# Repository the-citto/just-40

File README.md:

# Just 40

A 40% keyboard project, just 40 keys.

Staggered layout

Black unmarked [YMDK ultra slim low profile](https://ymdkey.com/search?q=Ultra-slim+Low+profile) for the control keys

[XVX Skyline R2](https://www.xvxchannel.com/en-gb/collections/low-profile-keycaps/products/xvx-skyline-r2) for alphas (which I like more for feel and sound)

[Waveshare RP2350-Tiny Development Board](https://www.waveshare.com/wiki/RP2350-Tiny)

[NeoPixel Reverse Mount RGB LEDs](https://www.digikey.co.uk/en/products/detail/adafruit-industries-llc/4960/14302512)

[Gateron KS-33 Low Profile 2.0 Banana Switch](https://www.gateron.com/products/gateron-ks-33-low-profile-20-banana-switch?VariantsId=10734)
soldered for plateless mount

PCB developed with KiCAD

Front

Back

#### Alternatives / Inspirations
I've searched for quite some time for 40% offerings, the most interesting to me
 - [Vortex Core Plus](https://vortexgear.store/products/core-plus)
 - [Litl keyboard](https://sthlmkb.com/shop/litl-keyboard-kit/)
 - [Skelett 40](https://novelkeys.com/collections/keyboards/products/skelett-40-keyboard-kit)

## coming soon

Micropython code

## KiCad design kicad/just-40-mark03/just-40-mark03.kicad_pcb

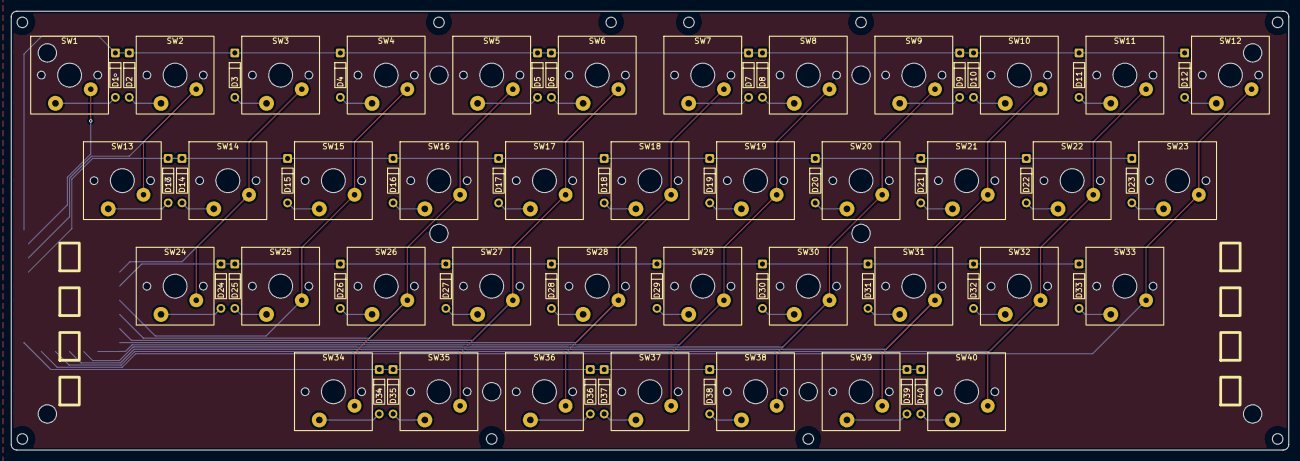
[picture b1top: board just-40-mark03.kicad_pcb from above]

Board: 2 copper layers, 230.0 x 79.0 mm, 100 parts (0 on the bottom side), 56 nets.

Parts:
A1: RP2350-Tiny; RP2350-Tiny-SMD
D1, D2, D3, D4, D5, D6, D7, D8, D9, D10, D11, D12, D13, D14, D15, D16, D17, D18, D19, D20, D21, D22, D23, D24, D25, D26, D27, D28, D29, D30, D31, D32, D33, D34, D35, D36, D37, D38, D39, D40: 1N4148; 1N4148_3
H1, H2, H3, H4, H5, H6, H7, H8: mount-hole; hole-mount
H9: RP2350-Tiny-USB; RP2350-Tiny-USB-3
H10, H11, H12, H13, H14, H15, H16, H17, H18, H19: mount-hole; hole-foot
SW1, SW2, SW3, SW4, SW5, SW6, SW7, SW8, SW9, SW10, SW11, SW12, SW13, SW14, SW15, SW16, SW17, SW18, SW19, SW20, SW21, SW22, SW23, SW24, SW25, SW26, SW27, SW28, SW29, SW30, SW31, SW32, SW33, SW34, SW35, SW36, SW37, SW38, SW39, SW40: KS-33v3-1U_4

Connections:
COL_00_2: A1.1 (GPIO1), SW1.1 (A)
COL_01_2: A1.2 (GPIO2), SW2.1 (A), SW13.1 (A)
COL_02_2: A1.29 (GPIO29_ADC2), SW3.1 (A), SW14.1 (A), SW24.1 (A)
COL_03_2: A1.27 (GPIO27_ADC1), SW4.1 (A), SW15.1 (A), SW25.1 (A)
COL_04_2: A1.26 (GPIO26_ADC0), SW5.1 (A), SW16.1 (A), SW26.1 (A), SW34.1 (A)
COL_05_2: A1.15 (GPIO15), SW6.1 (A), SW17.1 (A), SW27.1 (A), SW35.1 (A)
COL_06_2: A1.14 (GPIO14), SW7.1 (A), SW18.1 (A), SW28.1 (A), SW36.1 (A)
COL_07_2: A1.13 (GPIO13), SW8.1 (A), SW19.1 (A), SW29.1 (A), SW37.1 (A)
COL_08_2: A1.12 (GPIO12), SW9.1 (A), SW20.1 (A), SW30.1 (A), SW38.1 (A)
COL_09_2: A1.11 (GPIO11), SW10.1 (A), SW21.1 (A), SW31.1 (A), SW39.1 (A)
COL_10_2: A1.10 (GPIO10), SW11.1 (A), SW22.1 (A), SW32.1 (A), SW40.1 (A)
COL_11_2: A1.9 (GPIO9), SW12.1 (A), SW23.1 (A), SW33.1 (A)
unnamed: D1.A, SW1.2 (B)
unnamed: D2.A, SW2.2 (B)
unnamed: D3.A, SW3.2 (B)
unnamed: D4.A, SW4.2 (B)
unnamed: D5.A, SW5.2 (B)
unnamed: D6.A, SW6.2 (B)
unnamed: D7.A, SW7.2 (B)
unnamed: D8.A, SW8.2 (B)
unnamed: D9.A, SW9.2 (B)
unnamed: D10.A, SW10.2 (B)
unnamed: D11.A, SW11.2 (B)
unnamed: D12.A, SW12.2 (B)
unnamed: D13.A, SW13.2 (B)
unnamed: D14.A, SW14.2 (B)
unnamed: D15.A, SW15.2 (B)
unnamed: D16.A, SW16.2 (B)
unnamed: D17.A, SW17.2 (B)
unnamed: D18.A, SW18.2 (B)
unnamed: D19.A, SW19.2 (B)
unnamed: D20.A, SW20.2 (B)
unnamed: D21.A, SW21.2 (B)
unnamed: D22.A, SW22.2 (B)
unnamed: D23.A, SW23.2 (B)
unnamed: D24.A, SW24.2 (B)
unnamed: D25.A, SW25.2 (B)
unnamed: D26.A, SW26.2 (B)
unnamed: D27.A, SW27.2 (B)
unnamed: D28.A, SW28.2 (B)
unnamed: D29.A, SW29.2 (B)
unnamed: D30.A, SW30.2 (B)
unnamed: D31.A, SW31.2 (B)
unnamed: D32.A, SW32.2 (B)
unnamed: D33.A, SW33.2 (B)
unnamed: D34.A, SW34.2 (B)
unnamed: D35.A, SW35.2 (B)
unnamed: D36.A, SW36.2 (B)
unnamed: D37.A, SW37.2 (B)
unnamed: D38.A, SW38.2 (B)
unnamed: D39.A, SW39.2 (B)
unnamed: D40.A, SW40.2 (B)
ROW_0_2: A1.0 (GPIO0), D1.K, D2.K, D3.K, D4.K, D5.K, D6.K, D7.K, D8.K, D9.K, D10.K, D11.K, D12.K
ROW_1_2: A1.3 (GPIO3), D13.K, D14.K, D15.K, D16.K, D17.K, D18.K, D19.K, D20.K, D21.K, D22.K, D23.K
ROW_2_2: A1.28 (GPIO28_ADC2), D24.K, D25.K, D26.K, D27.K, D28.K, D29.K, D30.K, D31.K, D32.K, D33.K
ROW_3_2: A1.8 (GPIO8), D34.K, D35.K, D36.K, D37.K, D38.K, D39.K, D40.K

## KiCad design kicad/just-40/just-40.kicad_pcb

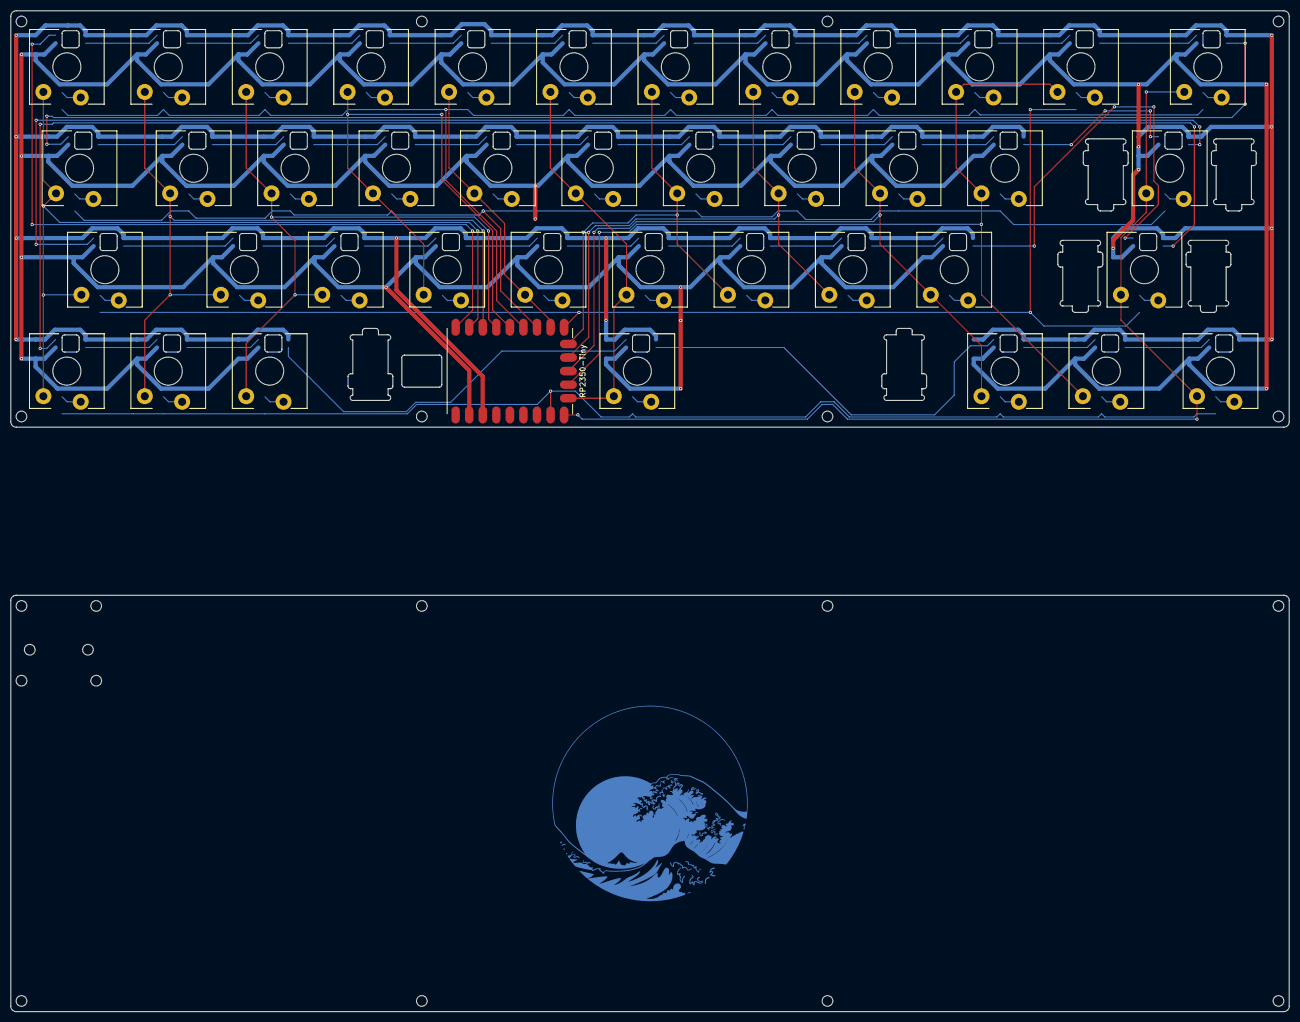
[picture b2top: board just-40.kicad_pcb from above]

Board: 2 copper layers, 239.5 x 78.0 mm, 57 parts (0 on the bottom side), 97 nets.

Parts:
A1, A2, A3, A4, A5, A6, A7, A8, A9, A10, A11, A14, A15, A16, A17, A18, A19, A20, A21, A22, A25, A26, A27, A28, A29, A30, A31, A32, A34, A35, A36, A38, A39: KEY-PARTS-HS; SW-LED-D-center-1U
A12: KEY-PARTS-HS; SW-LED-D-center-1.5U
A13, A40: KEY-PARTS-HS; SW-LED-D-center-1.25U
A23: KEY-PARTS-HS; SW-LED-D-center-2.25U
A24: KEY-PARTS-HS; SW-LED-D-center-1.75U
A33: KEY-PARTS-HS; SW-LED-D-center-2.75U
A37: KEY-PARTS-HS; SW-LED-D-center-6.25U
A41: RP2350-Tiny
H1, H2, H3, H4, H5, H6, H7, H8, H10, H11, H12, H13, H14, H15, H16: mount-hole; Mount-Hole
H9: RP2350-Tiny-USB

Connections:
COL_00: A1.A, A13.A, A24.A, A34.A, A41.1 (GPIO1)
COL_01: A2.A, A14.A, A25.A, A35.A, A41.2 (GPIO2)
COL_02: A3.A, A15.A, A26.A, A36.A, A41.3 (GPIO3)
COL_03: A4.A, A16.A, A27.A, A41.4 (GPIO4)
COL_04: A5.A, A17.A, A28.A, A41.7 (GPIO7)
COL_05: A6.A, A18.A, A29.A, A37.A, A41.13 (GPIO13)
COL_06: A7.A, A19.A, A30.A, A41.9 (GPIO9)
COL_07: A8.A, A20.A, A31.A, A41.10 (GPIO10)
COL_08: A9.A, A21.A, A32.A, A38.A, A41.11 (GPIO11)
COL_09: A10.A, A11.A, A22.A, A39.A, A41.12 (GPIO12)
COL_10: A12.A, A23.A, A33.A, A40.A, A41.14 (GPIO14)
DIN: A1.4 (DIN), A41.0 (GPIO0)
GND: A1.3 (GND), A1.C_1, A2.3 (GND), A2.C_1, A3.3 (GND), A3.C_1, A4.3 (GND), A4.C_1, A5.3 (GND), A5.C_1, A6.3 (GND), A6.C_1, A7.3 (GND), A7.C_1, A8.3 (GND), A8.C_1, A9.3 (GND), A9.C_1, A10.3 (GND), A10.C_1, A11.3 (GND), A11.C_1, A12.3 (GND), A12.C_1, A13.3 (GND), A13.C_1, A14.3 (GND), A14.C_1, A15.3 (GND), A15.C_1, A16.3 (GND), A16.C_1, A17.3 (GND), A17.C_1, A18.3 (GND), A18.C_1, A19.3 (GND), A19.C_1, A20.3 (GND), A20.C_1, A21.3 (GND), A21.C_1, A22.3 (GND), A22.C_1, A23.3 (GND), A23.C_1, A24.3 (GND), A24.C_1, A25.3 (GND), A25.C_1, A26.3 (GND), A26.C_1, A27.3 (GND), A27.C_1, A28.3 (GND), A28.C_1, A29.3 (GND), A29.C_1, A30.3 (GND), A30.C_1, A31.3 (GND), A31.C_1, A32.3 (GND), A32.C_1, A33.3 (GND), A33.C_1, A34.3 (GND), A34.C_1, A35.3 (GND), A35.C_1, A36.3 (GND), A36.C_1, A37.3 (GND), A37.C_1, A38.3 (GND), A38.C_1, A39.3 (GND), A39.C_1, A40.3 (GND), A40.C_1, A41.GND
unnamed: A1.2 (DOUT), A2.4 (DIN)
unnamed: A1.B, A1.D_1
unnamed: A2.2 (DOUT), A3.4 (DIN)
unnamed: A2.B, A2.D_1
unnamed: A3.2 (DOUT), A4.4 (DIN)
unnamed: A3.B, A3.D_1
unnamed: A4.2 (DOUT), A5.4 (DIN)
unnamed: A4.B, A4.D_1
unnamed: A5.2 (DOUT), A6.4 (DIN)
unnamed: A5.B, A5.D_1
unnamed: A6.2 (DOUT), A7.4 (DIN)
unnamed: A6.B, A6.D_1
unnamed: A7.2 (DOUT), A8.4 (DIN)
unnamed: A7.B, A7.D_1
unnamed: A8.2 (DOUT), A9.4 (DIN)
unnamed: A8.B, A8.D_1
unnamed: A9.B, A9.D_1
unnamed: A9.2 (DOUT), A10.4 (DIN)
unnamed: A10.2 (DOUT), A11.4 (DIN)
unnamed: A10.B, A10.D_1
unnamed: A11.2 (DOUT), A12.4 (DIN)
unnamed: A11.B, A11.D_1
unnamed: A12.2 (DOUT), A13.4 (DIN)
unnamed: A12.B, A12.D_1
unnamed: A13.2 (DOUT), A14.4 (DIN)
unnamed: A13.B, A13.D_1
unnamed: A14.2 (DOUT), A15.4 (DIN)
unnamed: A14.B, A14.D_1
unnamed: A15.2 (DOUT), A16.4 (DIN)
unnamed: A15.B, A15.D_1
unnamed: A16.2 (DOUT), A17.4 (DIN)
unnamed: A16.B, A16.D_1
unnamed: A17.2 (DOUT), A18.4 (DIN)
unnamed: A17.B, A17.D_1
unnamed: A18.2 (DOUT), A19.4 (DIN)
unnamed: A18.B, A18.D_1
unnamed: A19.2 (DOUT), A20.4 (DIN)
unnamed: A19.B, A19.D_1
unnamed: A20.2 (DOUT), A21.4 (DIN)
unnamed: A20.B, A20.D_1
unnamed: A21.2 (DOUT), A22.4 (DIN)
unnamed: A21.B, A21.D_1
unnamed: A22.2 (DOUT), A23.4 (DIN)
unnamed: A22.B, A22.D_1
unnamed: A23.2 (DOUT), A24.4 (DIN)
unnamed: A23.B, A23.D_1
unnamed: A24.2 (DOUT), A25.4 (DIN)
unnamed: A24.B, A24.D_1
unnamed: A25.2 (DOUT), A26.4 (DIN)
unnamed: A25.B, A25.D_1
unnamed: A26.2 (DOUT), A27.4 (DIN)
unnamed: A26.B, A26.D_1
unnamed: A27.2 (DOUT), A28.4 (DIN)
unnamed: A27.B, A27.D_1
unnamed: A28.2 (DOUT), A29.4 (DIN)
unnamed: A28.B, A28.D_1
unnamed: A29.2 (DOUT), A30.4 (DIN)
unnamed: A29.B, A29.D_1
unnamed: A30.2 (DOUT), A31.4 (DIN)
unnamed: A30.B, A30.D_1
unnamed: A31.2 (DOUT), A32.4 (DIN)
unnamed: A31.B, A31.D_1
unnamed: A32.2 (DOUT), A33.4 (DIN)
unnamed: A32.B, A32.D_1
unnamed: A33.2 (DOUT), A34.4 (DIN)
unnamed: A33.B, A33.D_1
unnamed: A34.2 (DOUT), A35.4 (DIN)
unnamed: A34.B, A34.D_1
unnamed: A35.2 (DOUT), A36.4 (DIN)
unnamed: A35.B, A35.D_1
unnamed: A36.2 (DOUT), A37.4 (DIN)
unnamed: A36.B, A36.D_1
unnamed: A37.2 (DOUT), A38.4 (DIN)
unnamed: A37.B, A37.D_1
unnamed: A38.2 (DOUT), A39.4 (DIN)
unnamed: A38.B, A38.D_1
unnamed: A39.2 (DOUT), A40.4 (DIN)
unnamed: A39.B, A39.D_1
unnamed: A40.B, A40.D_1
ROW_0: A1.D_2, A2.D_2, A3.D_2, A4.D_2, A5.D_2, A6.D_2, A7.D_2, A8.D_2, A9.D_2, A10.D_2, A12.D_2, A41.5 (GPIO5)
ROW_1: A13.D_2, A14.D_2, A15.D_2, A16.D_2, A17.D_2, A18.D_2, A19.D_2, A20.D_2, A21.D_2, A22.D_2, A23.D_2, A41.6 (GPIO6)
ROW_2: A11.D_2, A24.D_2, A25.D_2, A26.D_2, A27.D_2, A28.D_2, A29.D_2, A30.D_2, A31.D_2, A32.D_2, A33.D_2, A41.8 (GPIO8)
ROW_3: A34.D_2, A35.D_2, A36.D_2, A37.D_2, A38.D_2, A39.D_2, A40.D_2, A41.15 (GPIO15)
V_LED: A1.1 (VDD), A1.C_2, A2.1 (VDD), A2.C_2, A3.1 (VDD), A3.C_2, A4.1 (VDD), A4.C_2, A5.1 (VDD), A5.C_2, A6.1 (VDD), A6.C_2, A7.1 (VDD), A7.C_2, A8.1 (VDD), A8.C_2, A9.1 (VDD), A9.C_2, A10.1 (VDD), A10.C_2, A11.1 (VDD), A11.C_2, A12.1 (VDD), A12.C_2, A13.1 (VDD), A13.C_2, A14.1 (VDD), A14.C_2, A15.1 (VDD), A15.C_2, A16.1 (VDD), A16.C_2, A17.1 (VDD), A17.C_2, A18.1 (VDD), A18.C_2, A19.1 (VDD), A19.C_2, A20.1 (VDD), A20.C_2, A21.1 (VDD), A21.C_2, A22.1 (VDD), A22.C_2, A23.1 (VDD), A23.C_2, A24.1 (VDD), A24.C_2, A25.1 (VDD), A25.C_2, A26.1 (VDD), A26.C_2, A27.1 (VDD), A27.C_2, A28.1 (VDD), A28.C_2, A29.1 (VDD), A29.C_2, A30.1 (VDD), A30.C_2, A31.1 (VDD), A31.C_2, A32.1 (VDD), A32.C_2, A33.1 (VDD), A33.C_2, A34.1 (VDD), A34.C_2, A35.1 (VDD), A35.C_2, A36.1 (VDD), A36.C_2, A37.1 (VDD), A37.C_2, A38.1 (VDD), A38.C_2, A39.1 (VDD), A39.C_2, A40.1 (VDD), A40.C_2, A41.3V3

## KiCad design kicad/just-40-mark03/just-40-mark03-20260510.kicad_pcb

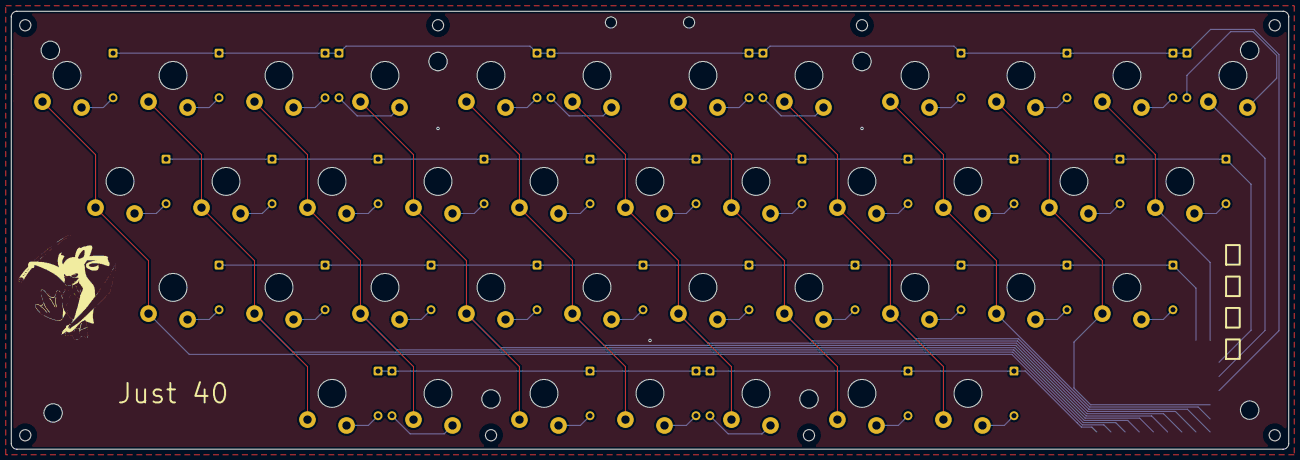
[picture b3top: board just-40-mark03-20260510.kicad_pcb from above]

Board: 2 copper layers, 229.0 x 78.5 mm, 98 parts (0 on the bottom side), 56 nets.

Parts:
A2: RP2350-Zero; RP2350-Tiny-SMD_1
D41, D42, D43, D44, D45, D46, D47, D48, D49, D50, D51, D52, D53, D54, D55, D56, D57, D58, D59, D60, D61, D62, D63, D64, D65, D66, D67, D68, D69, D70, D71, D72, D73, D74, D75, D76, D77, D78, D79, D80: 1N4148
H17, H18, H19, H20, H21, H22, H23, H24: mount-hole; hole-mount
H25, H26, H27, H28, H29, H30, H31, H32: mount-hole; hole-foot
H33: RP2350-Tiny-USB; RP2350-Tiny-USB-3
SW41, SW42, SW43, SW44, SW45, SW46, SW47, SW48, SW49, SW50, SW51, SW52, SW53, SW54, SW55, SW56, SW57, SW58, SW59, SW60, SW61, SW62, SW63, SW64, SW65, SW66, SW67, SW68, SW69, SW70, SW71, SW72, SW73, SW74, SW75, SW76, SW77, SW78, SW79, SW80: KS-33-1U_1

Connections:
COL_800_2: A2.1 (GPIO1), SW41.1 (A), SW53.1 (A), SW64.1 (A)
COL_801_2: A2.2 (GPIO2), SW42.1 (A), SW54.1 (A), SW65.1 (A), SW74.1 (A)
COL_802_2: A2.3 (GPIO3), SW43.1 (A), SW55.1 (A), SW66.1 (A), SW75.1 (A)
COL_803_2: A2.4 (GPIO4), SW44.1 (A), SW56.1 (A), SW67.1 (A), SW76.1 (A)
COL_804_2: A2.5 (GPIO5), SW45.1 (A), SW57.1 (A), SW68.1 (A), SW77.1 (A)
COL_805_2: A2.6 (GPIO6), SW46.1 (A), SW58.1 (A), SW69.1 (A), SW78.1 (A)
COL_806_2: A2.7 (GPIO7), SW47.1 (A), SW59.1 (A), SW70.1 (A), SW79.1 (A)
COL_807_2: A2.8 (GPIO8), SW48.1 (A), SW60.1 (A), SW71.1 (A), SW80.1 (A)
COL_808_2: A2.9 (GPIO9), SW49.1 (A), SW61.1 (A), SW72.1 (A)
COL_809_2: A2.10 (GPIO10), SW50.1 (A), SW62.1 (A), SW73.1 (A)
COL_810_2: A2.14 (GPIO14), SW51.1 (A), SW63.1 (A)
COL_811_2: A2.12 (GPIO12), SW52.1 (A)
unnamed: D41.A, SW41.2 (B)
unnamed: D42.A, SW42.2 (B)
unnamed: D43.A, SW43.2 (B)
unnamed: D44.A, SW44.2 (B)
unnamed: D45.A, SW45.2 (B)
unnamed: D46.A, SW46.2 (B)
unnamed: D47.A, SW47.2 (B)
unnamed: D48.A, SW48.2 (B)
unnamed: D49.A, SW49.2 (B)
unnamed: D50.A, SW50.2 (B)
unnamed: D51.A, SW51.2 (B)
unnamed: D52.A, SW52.2 (B)
unnamed: D53.A, SW53.2 (B)
unnamed: D54.A, SW54.2 (B)
unnamed: D55.A, SW55.2 (B)
unnamed: D56.A, SW56.2 (B)
unnamed: D57.A, SW57.2 (B)
unnamed: D58.A, SW58.2 (B)
unnamed: D59.A, SW59.2 (B)
unnamed: D60.A, SW60.2 (B)
unnamed: D61.A, SW61.2 (B)
unnamed: D62.A, SW62.2 (B)
unnamed: D63.A, SW63.2 (B)
unnamed: D64.A, SW64.2 (B)
unnamed: D65.A, SW65.2 (B)
unnamed: D66.A, SW66.2 (B)
unnamed: D67.A, SW67.2 (B)
unnamed: D68.A, SW68.2 (B)
unnamed: D69.A, SW69.2 (B)
unnamed: D70.A, SW70.2 (B)
unnamed: D71.A, SW71.2 (B)
unnamed: D72.A, SW72.2 (B)
unnamed: D73.A, SW73.2 (B)
unnamed: D74.A, SW74.2 (B)
unnamed: D75.A, SW75.2 (B)
unnamed: D76.A, SW76.2 (B)
unnamed: D77.A, SW77.2 (B)
unnamed: D78.A, SW78.2 (B)
unnamed: D79.A, SW79.2 (B)
unnamed: D80.A, SW80.2 (B)
ROW_80_2: A2.11 (GPIO11), D41.K, D42.K, D43.K, D44.K, D45.K, D46.K, D47.K, D48.K, D49.K, D50.K, D51.K, D52.K
ROW_81_2: A2.13 (GPIO13), D53.K, D54.K, D55.K, D56.K, D57.K, D58.K, D59.K, D60.K, D61.K, D62.K, D63.K
ROW_82_2: A2.15 (GPIO15), D64.K, D65.K, D66.K, D67.K, D68.K, D69.K, D70.K, D71.K, D72.K, D73.K
ROW_83_2: A2.0 (GPIO0), D74.K, D75.K, D76.K, D77.K, D78.K, D79.K, D80.K

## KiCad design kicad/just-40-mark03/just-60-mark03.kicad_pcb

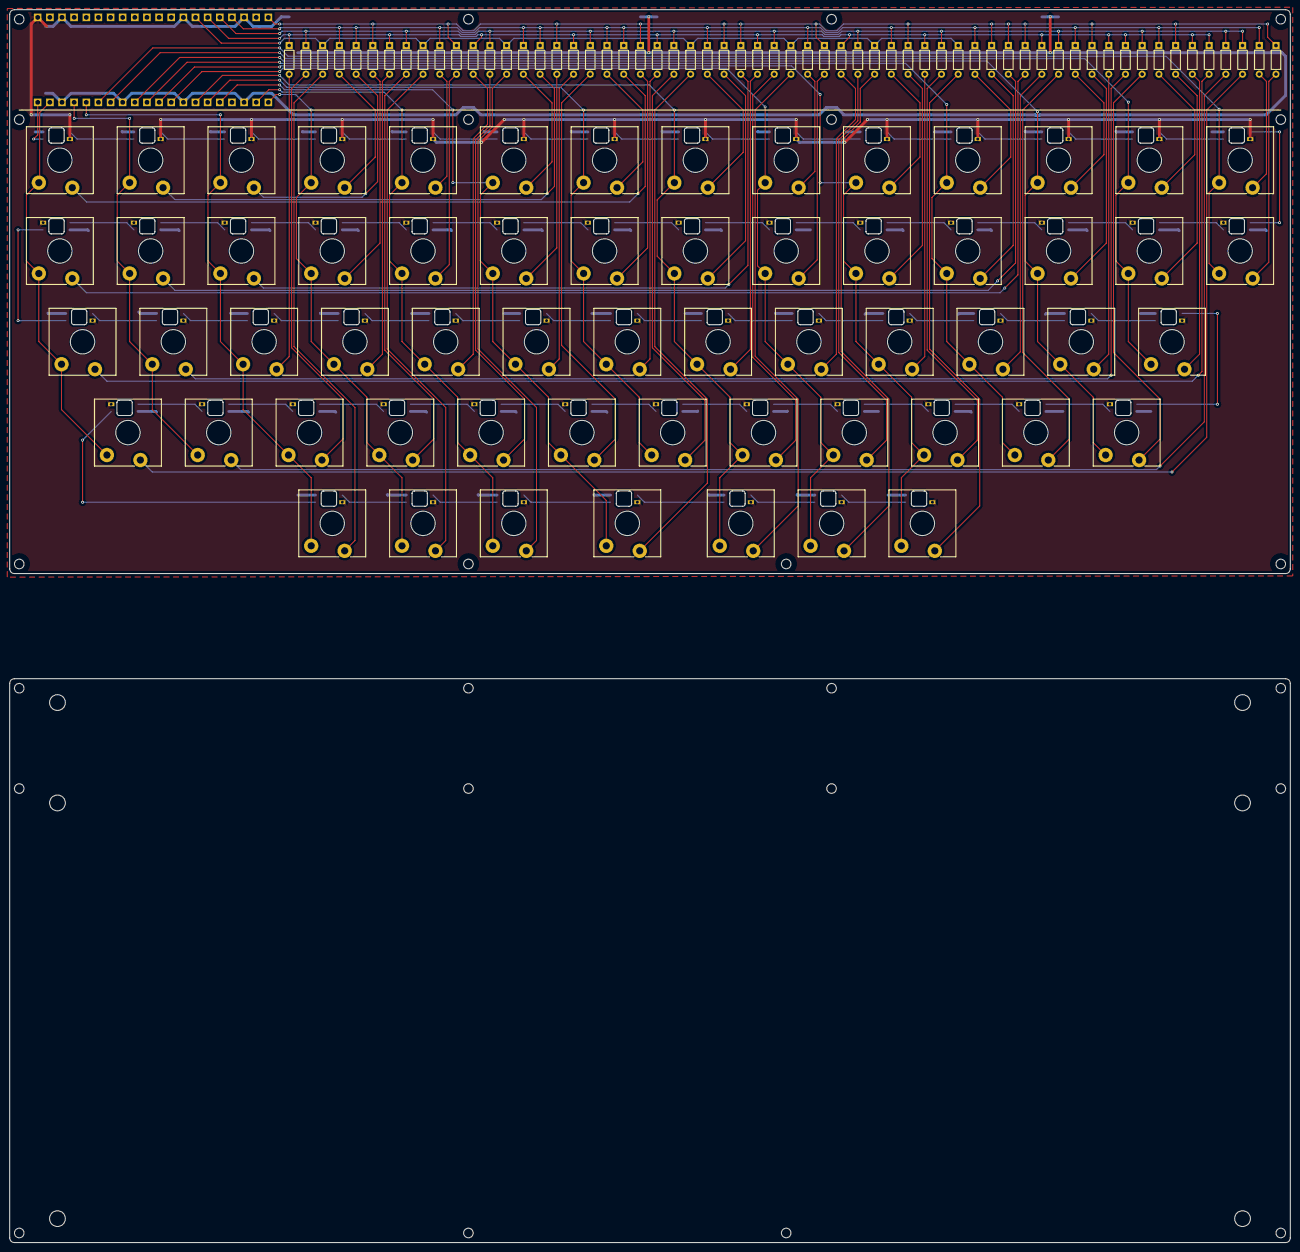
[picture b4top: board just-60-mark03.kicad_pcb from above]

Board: 2 copper layers, 268.0 x 118.0 mm, 151 parts (0 on the bottom side), 141 nets.

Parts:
A1, A2, A3, A4, A5, A6, A7, A8, A9, A10, A11, A12, A13, A14, A29, A30, A31, A32, A33, A34, A35, A36, A37, A38, A39, A40, A41, A54, A55, A56, A57, A58, A59, A60: KS-33-1U-LED-right
A15, A16, A17, A18, A19, A20, A21, A22, A23, A24, A25, A26, A27, A28, A42, A43, A44, A45, A46, A47, A48, A49, A50, A51, A52, A53: KS-33-1U-LED-left
D1, D2, D3, D4, D5, D6, D7, D8, D9, D10, D11, D12, D13, D14, D15, D16, D17, D18, D19, D20, D21, D22, D23, D24, D25, D26, D27, D28, D29, D30, D31, D32, D33, D34, D35, D36, D37, D38, D39, D40, D41, D42, D43, D44, D45, D46, D47, D48, D49, D50, D51, D52, D53, D54, D55, D56, D57, D58, D59, D60: 1N4148
H1, H2, H3, H4, H5, H6: hole-foot
H7, H8, H9, H10, H11, H12, H13, H14, H15, H16, H17, H18, H19, H20, H21, H22, H23, H24, H25, H26, H27, H28, H29, H30: hole-mount
U1: PICO-2

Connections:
COL_00: A1.A, A15.A, A29.A, A42.A, U1.2 (GPIO1)
COL_01: A2.A, A16.A, A30.A, A43.A, U1.4 (GPIO2)
COL_02: A3.A, A17.A, A31.A, A44.A, A54.A, U1.5 (GPIO3)
COL_03: A4.A, A18.A, A32.A, A45.A, A55.A, U1.20 (GPIO15)
COL_04: A5.A, A19.A, A33.A, A46.A, A56.A, U1.19 (GPIO14)
COL_05: A6.A, A20.A, A34.A, A47.A, A57.A, U1.16 (GPIO12)
COL_06: A7.A, A21.A, A35.A, A48.A, U1.15 (GPIO11)
COL_07: A8.A, A22.A, A36.A, A49.A, A58.A, U1.14 (GPIO10)
COL_08: A9.A, A23.A, A37.A, A50.A, A59.A, U1.12 (GPIO9)
COL_09: A10.A, A24.A, A38.A, A51.A, A60.A, U1.11 (GPIO8)
COL_10: A11.A, A25.A, A39.A, A52.A, U1.10 (GPIO7)
COL_11: A12.A, A26.A, A40.A, A53.A, U1.9 (GPIO6)
COL_12: A13.A, A27.A, A41.A, U1.7 (GPIO5)
COL_13: A14.A, A28.A, U1.6 (GPIO4)
DIN: A1.4 (DIN), U1.1 (GPIO0)
GND: A1.3 (GND), A2.3 (GND), A3.3 (GND), A4.3 (GND), A5.3 (GND), A6.3 (GND), A7.3 (GND), A8.3 (GND), A9.3 (GND), A10.3 (GND), A11.3 (GND), A12.3 (GND), A13.3 (GND), A14.3 (GND), A15.3 (GND), A16.3 (GND), A17.3 (GND), A18.3 (GND), A19.3 (GND), A20.3 (GND), A21.3 (GND), A22.3 (GND), A23.3 (GND), A24.3 (GND), A25.3 (GND), A26.3 (GND), A27.3 (GND), A28.3 (GND), A29.3 (GND), A30.3 (GND), A31.3 (GND), A32.3 (GND), A33.3 (GND), A34.3 (GND), A35.3 (GND), A36.3 (GND), A37.3 (GND), A38.3 (GND), A39.3 (GND), A40.3 (GND), A41.3 (GND), A42.3 (GND), A43.3 (GND), A44.3 (GND), A45.3 (GND), A46.3 (GND), A47.3 (GND), A48.3 (GND), A49.3 (GND), A50.3 (GND), A51.3 (GND), A52.3 (GND), A53.3 (GND), A54.3 (GND), A55.3 (GND), A56.3 (GND), A57.3 (GND), A58.3 (GND), A59.3 (GND), A60.3 (GND), U1.3 (GND), U1.8 (GND), U1.13 (GND), U1.18 (GND), U1.23 (GND), U1.28 (GND), U1.38 (GND)
unnamed: A1.2 (DOUT), A2.4 (DIN)
unnamed: A2.2 (DOUT), A3.4 (DIN)
unnamed: A3.2 (DOUT), A4.4 (DIN)
unnamed: A4.2 (DOUT), A5.4 (DIN)
unnamed: A5.2 (DOUT), A6.4 (DIN)
unnamed: A6.2 (DOUT), A7.4 (DIN)
unnamed: A7.2 (DOUT), A8.4 (DIN)
unnamed: A8.2 (DOUT), A9.4 (DIN)
unnamed: A9.2 (DOUT), A10.4 (DIN)
unnamed: A10.2 (DOUT), A11.4 (DIN)
unnamed: A11.2 (DOUT), A12.4 (DIN)
unnamed: A12.2 (DOUT), A13.4 (DIN)
unnamed: A13.2 (DOUT), A14.4 (DIN)
unnamed: A14.2 (DOUT), A28.4 (DIN)
unnamed: A15.4 (DIN), A16.2 (DOUT)
unnamed: A15.2 (DOUT), A29.4 (DIN)
unnamed: A16.4 (DIN), A17.2 (DOUT)
unnamed: A17.4 (DIN), A18.2 (DOUT)
unnamed: A18.4 (DIN), A19.2 (DOUT)
unnamed: A19.4 (DIN), A20.2 (DOUT)
unnamed: A20.4 (DIN), A21.2 (DOUT)
unnamed: A21.4 (DIN), A22.2 (DOUT)
unnamed: A22.4 (DIN), A23.2 (DOUT)
unnamed: A23.4 (DIN), A24.2 (DOUT)
unnamed: A24.4 (DIN), A25.2 (DOUT)
unnamed: A25.4 (DIN), A26.2 (DOUT)
unnamed: A26.4 (DIN), A27.2 (DOUT)
unnamed: A27.4 (DIN), A28.2 (DOUT)
unnamed: A29.2 (DOUT), A30.4 (DIN)
unnamed: A30.2 (DOUT), A31.4 (DIN)
unnamed: A31.2 (DOUT), A32.4 (DIN)
unnamed: A32.2 (DOUT), A33.4 (DIN)
unnamed: A33.2 (DOUT), A34.4 (DIN)
unnamed: A34.2 (DOUT), A35.4 (DIN)
unnamed: A35.2 (DOUT), A36.4 (DIN)
unnamed: A36.2 (DOUT), A37.4 (DIN)
unnamed: A37.2 (DOUT), A38.4 (DIN)
unnamed: A38.2 (DOUT), A39.4 (DIN)
unnamed: A39.2 (DOUT), A40.4 (DIN)
unnamed: A40.2 (DOUT), A41.4 (DIN)
unnamed: A41.2 (DOUT), A53.4 (DIN)
unnamed: A42.4 (DIN), A43.2 (DOUT)
unnamed: A42.2 (DOUT), A54.4 (DIN)
unnamed: A43.4 (DIN), A44.2 (DOUT)
unnamed: A44.4 (DIN), A45.2 (DOUT)
unnamed: A45.4 (DIN), A46.2 (DOUT)
unnamed: A46.4 (DIN), A47.2 (DOUT)
unnamed: A47.4 (DIN), A48.2 (DOUT)
unnamed: A48.4 (DIN), A49.2 (DOUT)
unnamed: A49.4 (DIN), A50.2 (DOUT)
unnamed: A50.4 (DIN), A51.2 (DOUT)
unnamed: A51.4 (DIN), A52.2 (DOUT)
unnamed: A52.4 (DIN), A53.2 (DOUT)
unnamed: A54.2 (DOUT), A55.4 (DIN)
unnamed: A55.2 (DOUT), A56.4 (DIN)
unnamed: A56.2 (DOUT), A57.4 (DIN)
unnamed: A57.2 (DOUT), A58.4 (DIN)
unnamed: A58.2 (DOUT), A59.4 (DIN)
unnamed: A59.2 (DOUT), A60.4 (DIN)
unnamed: A1.B, D1.2 (A)
unnamed: A2.B, D2.2 (A)
unnamed: A3.B, D3.2 (A)
unnamed: A4.B, D4.2 (A)
unnamed: A5.B, D5.2 (A)
unnamed: A6.B, D6.2 (A)
unnamed: A7.B, D7.2 (A)
unnamed: A8.B, D8.2 (A)
unnamed: A9.B, D9.2 (A)
unnamed: A10.B, D10.2 (A)
unnamed: A11.B, D11.2 (A)
unnamed: A12.B, D12.2 (A)
unnamed: A13.B, D13.2 (A)
unnamed: A14.B, D14.2 (A)
unnamed: A15.B, D15.2 (A)
unnamed: A16.B, D16.2 (A)
unnamed: A17.B, D17.2 (A)
unnamed: A18.B, D18.2 (A)
unnamed: A19.B, D19.2 (A)
unnamed: A20.B, D20.2 (A)
unnamed: A21.B, D21.2 (A)
unnamed: A22.B, D22.2 (A)
unnamed: A23.B, D23.2 (A)
unnamed: A24.B, D24.2 (A)
unnamed: A25.B, D25.2 (A)
unnamed: A26.B, D26.2 (A)
unnamed: A27.B, D27.2 (A)
unnamed: A28.B, D28.2 (A)
unnamed: A29.B, D29.2 (A)
unnamed: A30.B, D30.2 (A)
unnamed: A31.B, D31.2 (A)
unnamed: A32.B, D32.2 (A)
unnamed: A33.B, D33.2 (A)
unnamed: A34.B, D34.2 (A)
unnamed: A35.B, D35.2 (A)
unnamed: A36.B, D36.2 (A)
unnamed: A37.B, D37.2 (A)
unnamed: A38.B, D38.2 (A)
unnamed: A39.B, D39.2 (A)
unnamed: A40.B, D40.2 (A)
unnamed: A41.B, D41.2 (A)
unnamed: A42.B, D42.2 (A)
unnamed: A43.B, D43.2 (A)
unnamed: A44.B, D44.2 (A)
unnamed: A45.B, D45.2 (A)
unnamed: A46.B, D46.2 (A)
unnamed: A47.B, D47.2 (A)
unnamed: A48.B, D48.2 (A)
unnamed: A49.B, D49.2 (A)
unnamed: A50.B, D50.2 (A)
unnamed: A51.B, D51.2 (A)
unnamed: A52.B, D52.2 (A)
unnamed: A53.B, D53.2 (A)
unnamed: A54.B, D54.2 (A)
unnamed: A55.B, D55.2 (A)
unnamed: A56.B, D56.2 (A)
unnamed: A57.B, D57.2 (A)
unnamed: A58.B, D58.2 (A)
unnamed: A59.B, D59.2 (A)
unnamed: A60.B, D60.2 (A)
ROW_0: D1.1 (K), D2.1 (K), D3.1 (K), D4.1 (K), D5.1 (K), D6.1 (K), D7.1 (K), D8.1 (K), D9.1 (K), D10.1 (K), D11.1 (K), D12.1 (K), D13.1 (K), D14.1 (K), U1.24 (GPIO18)
ROW_1: D15.1 (K), D16.1 (K), D17.1 (K), D18.1 (K), D19.1 (K), D20.1 (K), D21.1 (K), D22.1 (K), D23.1 (K), D24.1 (K), D25.1 (K), D26.1 (K), D27.1 (K), D28.1 (K), U1.21 (GPIO16)
ROW_2: D29.1 (K), D30.1 (K), D31.1 (K), D32.1 (K), D33.1 (K), D34.1 (K), D35.1 (K), D36.1 (K), D37.1 (K), D38.1 (K), D39.1 (K), D40.1 (K), D41.1 (K), U1.26 (GPIO20)
ROW_3: D42.1 (K), D43.1 (K), D44.1 (K), D45.1 (K), D46.1 (K), D47.1 (K), D48.1 (K), D49.1 (K), D50.1 (K), D51.1 (K), D52.1 (K), D53.1 (K), U1.25 (GPIO19)
ROW_4: D54.1 (K), D55.1 (K), D56.1 (K), D57.1 (K), D58.1 (K), D59.1 (K), D60.1 (K), U1.27 (GPIO21)
V_LED: A1.1 (VDD), A2.1 (VDD), A3.1 (VDD), A4.1 (VDD), A5.1 (VDD), A6.1 (VDD), A7.1 (VDD), A8.1 (VDD), A9.1 (VDD), A10.1 (VDD), A11.1 (VDD), A12.1 (VDD), A13.1 (VDD), A14.1 (VDD), A15.1 (VDD), A16.1 (VDD), A17.1 (VDD), A18.1 (VDD), A19.1 (VDD), A20.1 (VDD), A21.1 (VDD), A22.1 (VDD), A23.1 (VDD), A24.1 (VDD), A25.1 (VDD), A26.1 (VDD), A27.1 (VDD), A28.1 (VDD), A29.1 (VDD), A30.1 (VDD), A31.1 (VDD), A32.1 (VDD), A33.1 (VDD), A34.1 (VDD), A35.1 (VDD), A36.1 (VDD), A37.1 (VDD), A38.1 (VDD), A39.1 (VDD), A40.1 (VDD), A41.1 (VDD), A42.1 (VDD), A43.1 (VDD), A44.1 (VDD), A45.1 (VDD), A46.1 (VDD), A47.1 (VDD), A48.1 (VDD), A49.1 (VDD), A50.1 (VDD), A51.1 (VDD), A52.1 (VDD), A53.1 (VDD), A54.1 (VDD), A55.1 (VDD), A56.1 (VDD), A57.1 (VDD), A58.1 (VDD), A59.1 (VDD), A60.1 (VDD), U1.40 (VBUS)

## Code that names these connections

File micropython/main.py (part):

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


# row_0 = machine.Pin(0, machine.Pin.IN, machine.Pin.PULL_DOWN)
# row_1 = machine.Pin(1, machine.Pin.IN, machine.Pin.PULL_DOWN)
# row_2 = machine.Pin(2, machine.Pin.IN, machine.Pin.PULL_DOWN)
#
# col_0 = machine.Pin(10, machine.Pin.OUT)
# col_1 = machine.Pin(11, machine.Pin.OUT)
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
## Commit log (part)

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2025-04-18 add README.md
2025-04-18 add KLEs
2025-04-18 improve KLEs
2025-04-19 add hardware/datasheets
2025-04-19 add datasheets
2025-04-19 add kle navigation layer
2025-04-19 amend kle navigation layer
2025-04-19 add punctuation layer
2025-04-20 add topic README.md
2025-04-20 update layers
2025-04-20 add .gitignore
2025-04-20 remove kicad backup dir
2025-04-21 add libraries
2025-04-21 wip libraries
2025-04-21 add footprints
2025-04-22 add hhkb kle
2025-04-29 wips
2025-05-06 wips kicad - start micropython
2025-05-11 lots of wip
2025-05-13 almost all routed
2025-05-13 pcb done - ground plate to do
2025-05-14 pcb ground plane done - add 3d images
2025-05-14 minor changes
2025-06-04 gerber ready
2025-06-04 pcb pics
2026-04-27 mark03
